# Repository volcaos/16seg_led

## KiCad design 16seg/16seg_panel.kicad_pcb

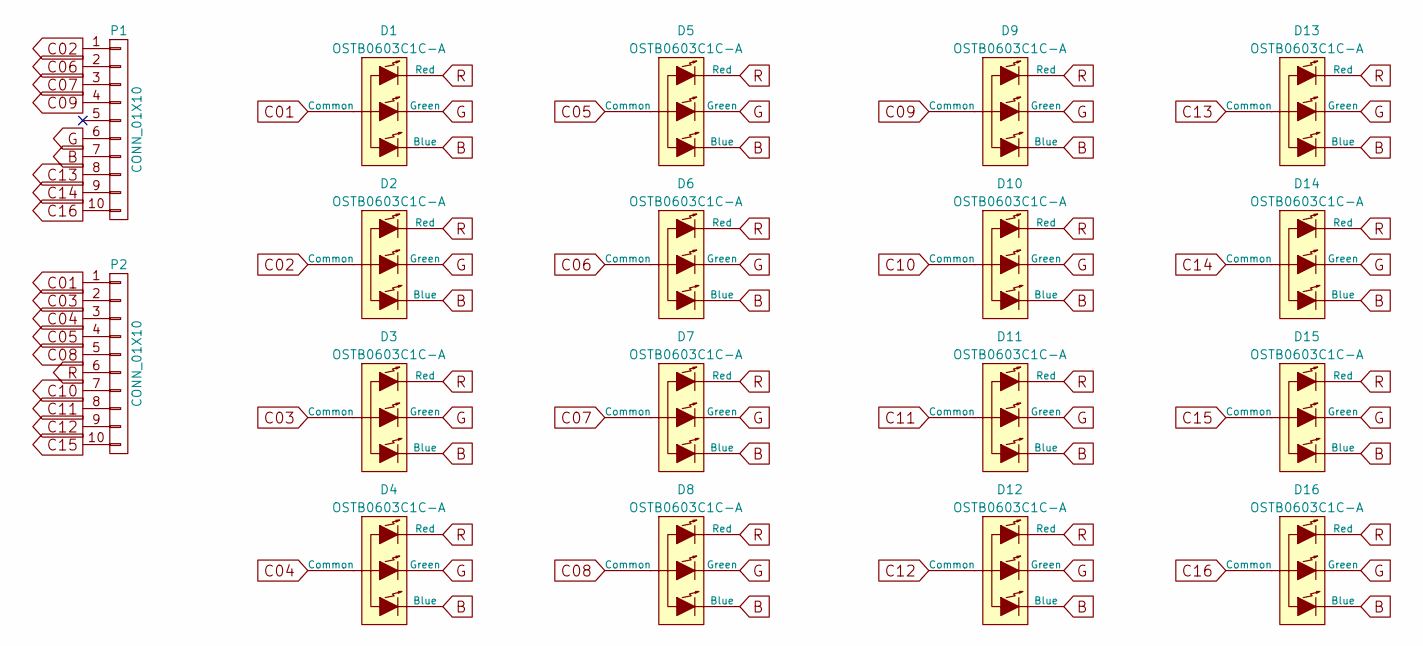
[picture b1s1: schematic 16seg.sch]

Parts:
D1, D2, D3, D4, D5, D6, D7, D8, D9, D10, D11, D12, D13, D14, D15, D16: OSTB0603C1C-A
P1, P2: CONN_01X10; Pin_Header_Straight_1x10_Pitch2.54mm

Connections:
B: D1.3 (Blue), D2.3 (Blue), D3.3 (Blue), D4.3 (Blue), D5.3 (Blue), D6.3 (Blue), D7.3 (Blue), D8.3 (Blue), D9.3 (Blue), D10.3 (Blue), D11.3 (Blue), D12.3 (Blue), D13.3 (Blue), D14.3 (Blue), D15.3 (Blue), D16.3 (Blue), P1.7
C01: D1.1 (Common), P2.1
C02: D2.1 (Common), P1.1
C03: D3.1 (Common), P2.2
C04: D4.1 (Common), P2.3
C05: D5.1 (Common), P2.4
C06: D6.1 (Common), P1.2
C07: D7.1 (Common), P1.3
C08: D8.1 (Common), P2.5
C09: D9.1 (Common), P1.4
C10: D10.1 (Common), P2.7
C11: D11.1 (Common), P2.8
C12: D12.1 (Common), P2.9
C13: D13.1 (Common), P1.8
C14: D14.1 (Common), P1.9
C15: D15.1 (Common), P2.10
C16: D16.1 (Common), P1.10
G: D1.4 (Green), D2.4 (Green), D3.4 (Green), D4.4 (Green), D5.4 (Green), D6.4 (Green), D7.4 (Green), D8.4 (Green), D9.4 (Green), D10.4 (Green), D11.4 (Green), D12.4 (Green), D13.4 (Green), D14.4 (Green), D15.4 (Green), D16.4 (Green), P1.6
R: D1.2 (Red), D2.2 (Red), D3.2 (Red), D4.2 (Red), D5.2 (Red), D6.2 (Red), D7.2 (Red), D8.2 (Red), D9.2 (Red), D10.2 (Red), D11.2 (Red), D12.2 (Red), D13.2 (Red), D14.2 (Red), D15.2 (Red), D16.2 (Red), P2.6

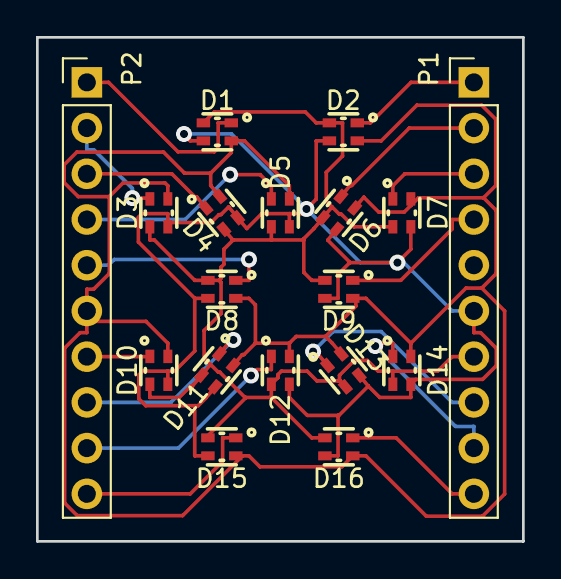
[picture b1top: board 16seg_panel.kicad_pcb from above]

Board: 2 copper layers, 27.0 x 28.0 mm, 18 parts (0 on the bottom side), 19 nets.
